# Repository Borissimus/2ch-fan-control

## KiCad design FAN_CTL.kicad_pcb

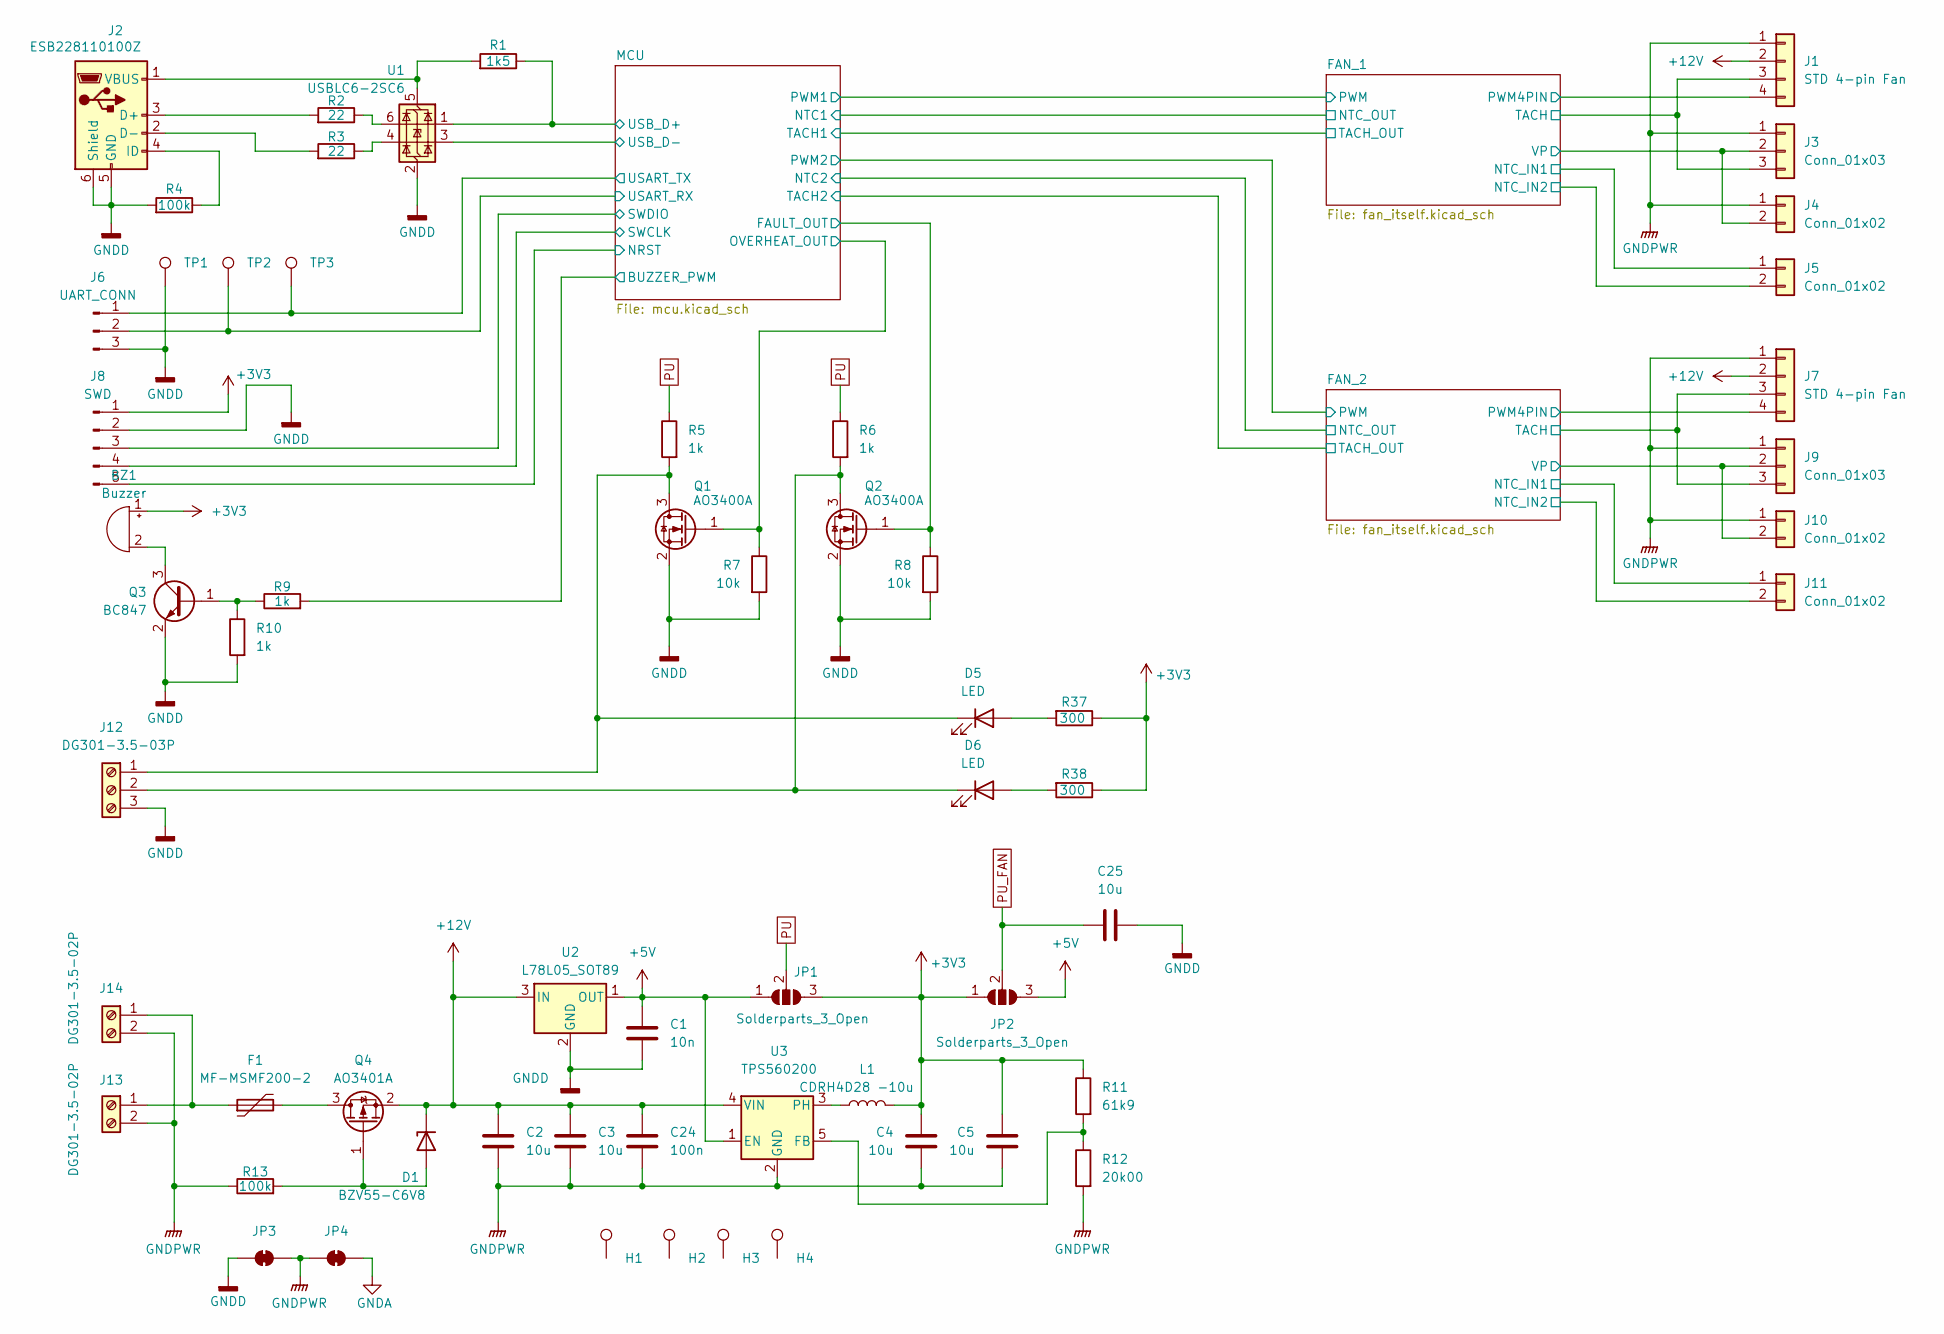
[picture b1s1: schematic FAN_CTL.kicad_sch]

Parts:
BZ1: Buzzer; Buzzer_TDK_PS1240P02BT_D12.2mm_H6.5mm
C1: 10n; C_0805_2012Metric
C2, C3, C4, C5, C25: 10u; C_0805_2012Metric
C24: 100n; C_0805_2012Metric
D1: BZV55-C6V8; D_MiniMELF
D5, D6: LED; LED_0805_2012Metric
F1: MF-MSMF200-2; Fuse_1812_4532Metric
H1, H2, H3, H4: parts; parts_3.2mm_M3_Pad_Via
J1, J7: STD 4-pin Fan; FanPinHeader_1x04_P2.54mm_Vertical
J2: ESB228110100Z; USB_Micro-B_Molex_47346-0001
J3, J9: Conn_01x03; FanPinHeader_1x03_P2.54mm_Vertical
J4, J10: Conn_01x02; JST_XH_B2B-XH-A_1x02_P2.50mm_Vertical
J5, J11: Conn_01x02; JST_PH_B2B-PH-K_1x02_P2.00mm_Vertical
J6: UART_CONN; PinHeader_1x03_P2.54mm_Vertical
J8: SWD; PinHeader_1x05_P2.54mm_Vertical
J12: DG301-3.5-03P; DG350-3_5-03P
J13, J14: DG301-3.5-02P; DG350-3_5-02P
JP1, JP2: Solderparts_3_Open; Solderparts-3_P1.3mm_Open_RoundedPad1.0x1.5mm
JP3, JP4: Solderparts_2_Bridged; Solderparts-2_P1.3mm_Bridged_Pad1.0x1.5mm
L1: CDRH4D28 -10u; CDRH4D28
Q1, Q2: AO3400A; SOT-23
Q3: BC847; SOT-23
Q4: AO3401A; SOT-23
R1: 1k5; R_0805_2012Metric
R2, R3: 22; R_0805_2012Metric
R4, R13: 100k; R_0805_2012Metric
R5, R6, R9, R10: 1k; R_0805_2012Metric
R7, R8: 10k; R_0805_2012Metric
R11: 61k9; R_0805_2012Metric
R12: 20k00; R_0805_2012Metric
R37, R38: 300; R_0805_2012Metric
TP1, TP2, TP3: parts; parts_Pad_D1.0mm
U1: USBLC6-2SC6; SOT-23-6
U2: L78L05_SOT89; SOT-89-3
U3: TPS560200; SOT-23-5

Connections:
+3.3VA: J5.1, J11.1; also elsewhere on the board
+3V3: BZ1.1 (+), C4.1, C5.1, J8.1, JP1.3 (B), JP2.1 (A), L1.2, R11.1, R37.1, R38.1; also elsewhere on the board
+5V: C1.1, JP1.1 (A), JP2.3 (B), U2.1 (OUT), U3.1 (EN)
+12V: C2.1, C3.1, C24.1, D1.1 (K), J1.2, J7.2, Q4.2 (S), U2.3 (IN), U3.4 (VIN); also elsewhere on the board
/FAN_1/NTC_IN2: J5.2; also elsewhere on the board
/FAN_1/PWM4PIN: J1.4; also elsewhere on the board
/FAN_1/TACH: J1.3, J3.3; also elsewhere on the board
/FAN_1/VP: J3.2, J4.2; also elsewhere on the board
/FAN_2/NTC_IN2: J11.2; also elsewhere on the board
/FAN_2/PWM4PIN: J7.4; also elsewhere on the board
/FAN_2/TACH: J7.3, J9.3; also elsewhere on the board
/FAN_2/VP: J9.2, J10.2; also elsewhere on the board
/MCU/BUZZER_PWM: R9.2; also elsewhere on the board
/MCU/FAULT_OUT: Q2.1 (G), R8.1; also elsewhere on the board
/MCU/NRST: J8.5; also elsewhere on the board
/MCU/OVERHEAT_OUT: Q1.1 (G), R7.1; also elsewhere on the board
/MCU/SWCLK: J8.4; also elsewhere on the board
/MCU/SWDIO: J8.3; also elsewhere on the board
/MCU/USART_RX: J6.2, TP2.1 (1_1); also elsewhere on the board
/MCU/USART_TX: J6.1, TP3.1 (1_1); also elsewhere on the board
/MCU/USB_D+: R1.1, U1.1 (I/O1); also elsewhere on the board
/MCU/USB_D-: U1.3 (I/O2); also elsewhere on the board
GNDA: JP4.2 (B); also elsewhere on the board
GNDD: C1.2, C25.2, J2.5 (GND), J2.6 (Shield), J6.3, J8.2, J12.3, JP3.1 (A), Q1.2 (S), Q2.2 (S), Q3.2 (E), R4.2, R7.2, R8.2, R10.2, TP1.1 (1_1), U1.2 (GND), U2.2 (GND); also elsewhere on the board
GNDPWR: C2.2, C3.2, C4.2, C5.2, C24.2, J1.1, J3.1, J4.1, J7.1, J9.1, J10.1, J13.2, J14.2, JP3.2 (B), JP4.1 (A), R12.2, R13.1, U3.2 (GND); also elsewhere on the board
unnamed: BZ1.2 (-), Q3.3 (C)
unnamed: D1.2 (A), Q4.1 (G), R13.2
unnamed: D5.2 (A), R37.2
unnamed: D5.1 (K), J12.1, Q1.3 (D), R5.2
unnamed: D6.2 (A), R38.2
unnamed: D6.1 (K), J12.2, Q2.3 (D), R6.2
unnamed: J2.3 (D+), R2.2
unnamed: J2.2 (D-), R3.2
unnamed: J2.4 (ID), R4.1
unnamed: J2.1 (VBUS), R1.2, U1.5 (VBUS)
unnamed: F1.1, J13.1, J14.1
unnamed: Q3.1 (B), R9.1, R10.1
unnamed: F1.2, Q4.3 (D)
unnamed: R2.1, U1.6 (I/O1)
unnamed: R3.1, U1.4 (I/O2)
unnamed: R11.2, R12.1, U3.5 (FB)
unnamed: L1.1, U3.3 (PH)
PU: JP1.2 (C), R5.1, R6.1
PU_FAN: C25.1, JP2.2 (C); also elsewhere on the board

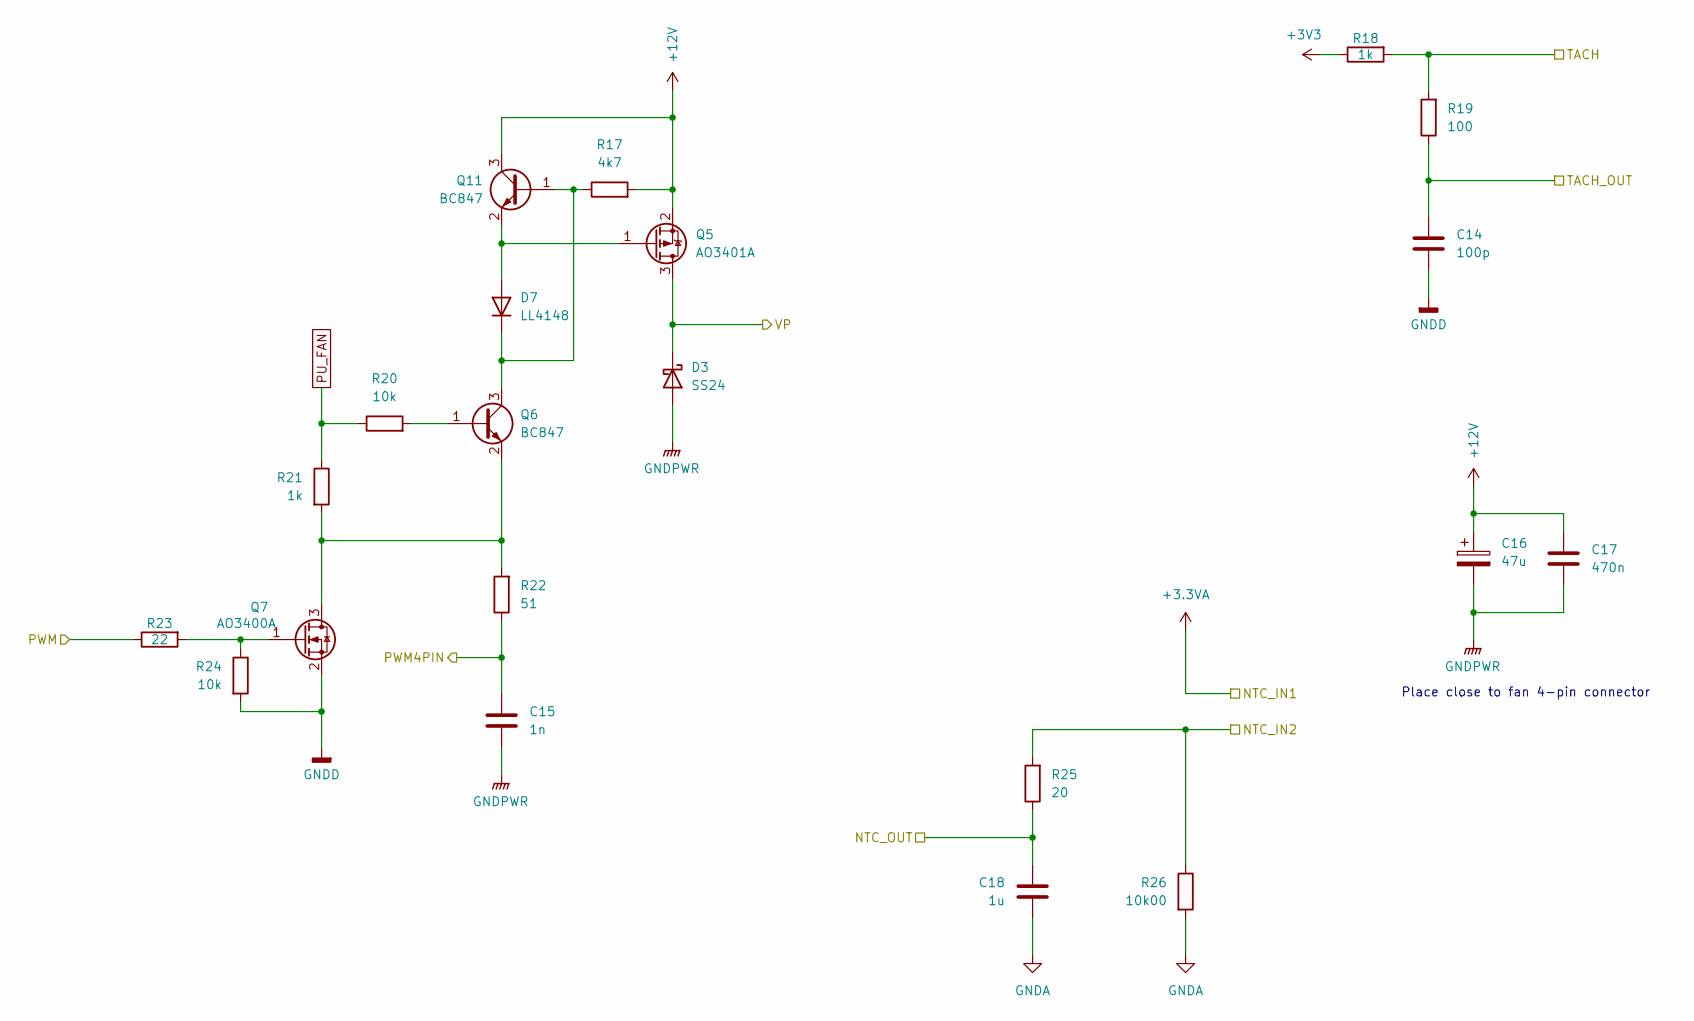
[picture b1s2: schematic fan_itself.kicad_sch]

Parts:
C14: 100p; C_0805_2012Metric
C15: 1n; C_0805_2012Metric
C16: 47u; CP_Radial_D5.0mm_P2.50mm
C17: 470n; C_0805_2012Metric
C18: 1u; C_0402_1005Metric
D3: SS24; D_SMA
D7: LL4148; D_MiniMELF
Q5: AO3401A; SOT-23
Q6, Q11: BC847; SOT-23
Q7: AO3400A; SOT-23
R17: 4k7; R_0805_2012Metric
R18, R21: 1k; R_0805_2012Metric
R19: 100; R_0805_2012Metric
R20, R24: 10k; R_0805_2012Metric
R22: 51; R_0805_2012Metric
R23: 22; R_0805_2012Metric
R25: 20; R_0402_1005Metric
R26: 10k00; R_0402_1005Metric

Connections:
+3V3: R18.1; also elsewhere on the board
+12V: C16.1, C17.1, Q5.2 (S), Q11.3 (C), R17.2; also elsewhere on the board
/FAN_1/NTC_IN2: R25.2, R26.1; also elsewhere on the board
/FAN_1/NTC_OUT: C18.1, R25.1; also elsewhere on the board
/FAN_1/PWM: R23.1; also elsewhere on the board
/FAN_1/PWM4PIN: C15.1, R22.1; also elsewhere on the board
/FAN_1/TACH: R18.2, R19.2; also elsewhere on the board
/FAN_1/TACH_OUT: C14.1, R19.1; also elsewhere on the board
/FAN_1/VP: D3.1 (K), Q5.3 (D); also elsewhere on the board
GNDA: C18.2, R26.2; also elsewhere on the board
GNDD: C14.2, Q7.2 (S), R24.2; also elsewhere on the board
GNDPWR: C15.2, C16.2, C17.2, D3.2 (A); also elsewhere on the board
unnamed: D7.2 (A), Q5.1 (G), Q11.2 (E)
unnamed: D7.1 (K), Q6.3 (C), Q11.1 (B), R17.1
unnamed: Q6.1 (B), R20.2
unnamed: Q6.2 (E), Q7.3 (D), R21.2, R22.2
unnamed: Q7.1 (G), R23.2, R24.1
PU_FAN: R20.1, R21.1; also elsewhere on the board

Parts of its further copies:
C19: 100p; C_0805_2012Metric
C20: 1n; C_0805_2012Metric
C21: 47u; CP_Radial_D5.0mm_P2.50mm
C22: 470n; C_0805_2012Metric
C23: 1u; C_0402_1005Metric
D4: SS24; D_SMA
D8: LL4148; D_MiniMELF
Q8: AO3401A; SOT-23
Q9, Q12: BC847; SOT-23
Q10: AO3400A; SOT-23
R27: 4k7; R_0805_2012Metric
R28, R31: 1k; R_0805_2012Metric
R29: 100; R_0805_2012Metric
R30, R34: 10k; R_0805_2012Metric
R32: 51; R_0805_2012Metric
R33: 22; R_0805_2012Metric
R35: 20; R_0402_1005Metric
R36: 10k00; R_0402_1005Metric

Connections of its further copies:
+3V3: R28.1; also elsewhere on the board
+12V: C21.1, C22.1, Q8.2 (S), Q12.3 (C), R27.2; also elsewhere on the board
/FAN_2/NTC_IN2: R35.2, R36.1; also elsewhere on the board
/FAN_2/NTC_OUT: C23.1, R35.1; also elsewhere on the board
/FAN_2/PWM: R33.1; also elsewhere on the board
/FAN_2/PWM4PIN: C20.1, R32.1; also elsewhere on the board
/FAN_2/TACH: R28.2, R29.2; also elsewhere on the board
/FAN_2/TACH_OUT: C19.1, R29.1; also elsewhere on the board
/FAN_2/VP: D4.1 (K), Q8.3 (D); also elsewhere on the board
GNDA: C23.2, R36.2; also elsewhere on the board
GNDD: C19.2, Q10.2 (S), R34.2; also elsewhere on the board
GNDPWR: C20.2, C21.2, C22.2, D4.2 (A); also elsewhere on the board
unnamed: D8.2 (A), Q8.1 (G), Q12.2 (E)
unnamed: D8.1 (K), Q9.3 (C), Q12.1 (B), R27.1
unnamed: Q9.1 (B), R30.2
unnamed: Q9.2 (E), Q10.3 (D), R31.2, R32.2
unnamed: Q10.1 (G), R33.2, R34.1
PU_FAN: R30.1, R31.1; also elsewhere on the board

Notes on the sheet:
Place close to fan 4-pin connector

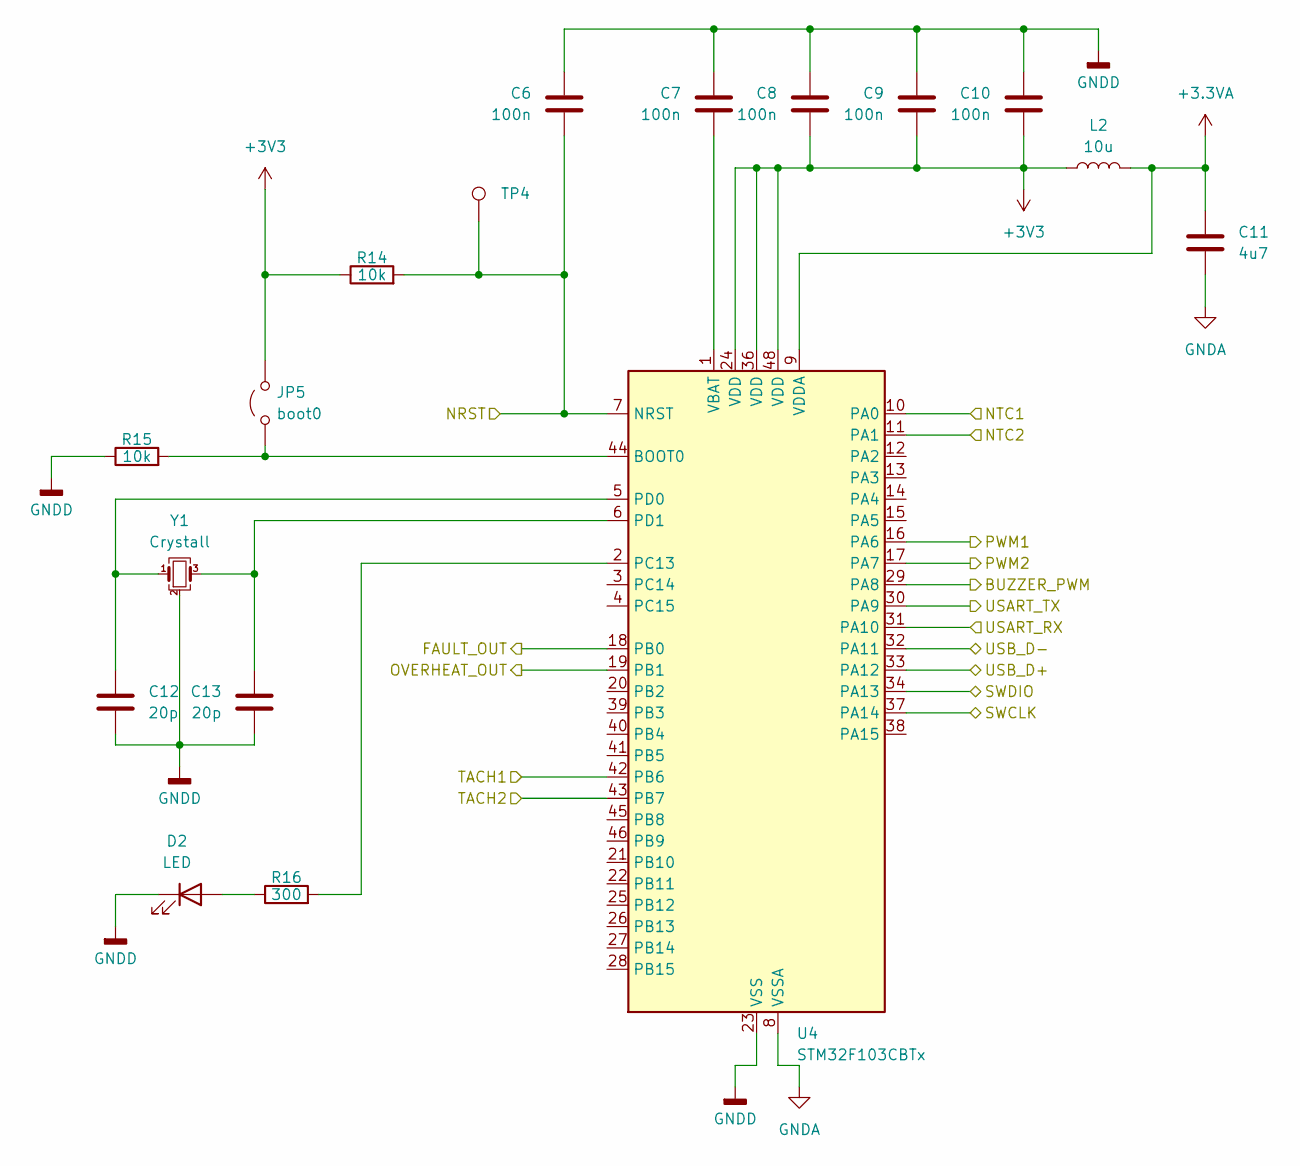
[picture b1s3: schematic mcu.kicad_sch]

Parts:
C6, C7, C8, C9, C10: 100n; C_0402_1005Metric
C11: 4u7; C_0603_1608Metric
C12, C13: 20p; C_0402_1005Metric
D2: LED; LED_0805_2012Metric
JP5: boot0; PinHeader_1x02_P2.54mm_Vertical
L2: 10u; L_1210_3225Metric
R14, R15: 10k; R_0805_2012Metric
R16: 300; R_0805_2012Metric
TP4: parts; parts_Pad_D1.0mm
U4: STM32F103CBTx; LQFP-48_7x7mm_P0.5mm
Y1: Crystall; Crystal_SMD_5032-4Pin_5.0x3.2mm

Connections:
+3.3VA: C11.1, L2.2, U4.9 (VDDA); also elsewhere on the board
+3V3: C8.2, C9.2, C10.2, JP5.2 (B), L2.1, R14.1, U4.24 (VDD), U4.36 (VDD), U4.48 (VDD); also elsewhere on the board
/FAN_1/NTC_OUT: U4.10 (PA0); also elsewhere on the board
/FAN_1/PWM: U4.16 (PA6); also elsewhere on the board
/FAN_1/TACH_OUT: U4.42 (PB6); also elsewhere on the board
/FAN_2/NTC_OUT: U4.11 (PA1); also elsewhere on the board
/FAN_2/PWM: U4.17 (PA7); also elsewhere on the board
/FAN_2/TACH_OUT: U4.43 (PB7); also elsewhere on the board
/MCU/BUZZER_PWM: U4.29 (PA8); also elsewhere on the board
/MCU/FAULT_OUT: U4.18 (PB0); also elsewhere on the board
/MCU/NRST: C6.2, R14.2, TP4.1 (1_1), U4.7 (NRST); also elsewhere on the board
/MCU/OVERHEAT_OUT: U4.19 (PB1); also elsewhere on the board
/MCU/SWCLK: U4.37 (PA14); also elsewhere on the board
/MCU/SWDIO: U4.34 (PA13); also elsewhere on the board
/MCU/USART_RX: U4.31 (PA10); also elsewhere on the board
/MCU/USART_TX: U4.30 (PA9); also elsewhere on the board
/MCU/USB_D+: U4.33 (PA12); also elsewhere on the board
/MCU/USB_D-: U4.32 (PA11); also elsewhere on the board
GNDA: C11.2, U4.8 (VSSA); also elsewhere on the board
GNDD: C6.1, C7.1, C8.1, C9.1, C10.1, C12.1, C13.1, D2.1 (K), R15.1, U4.23 (VSS), U4.35 (VSS), U4.47 (VSS), Y1.2 (G), Y1.4 (G); also elsewhere on the board
unnamed: D2.2 (A), R16.1
unnamed: JP5.1 (A), R15.2, U4.44 (BOOT0)
unnamed: R16.2, U4.2 (PC13)
unnamed: C12.2, U4.5 (PD0), Y1.1
unnamed: C13.2, U4.6 (PD1), Y1.3
unnamed: C7.2, U4.1 (VBAT)

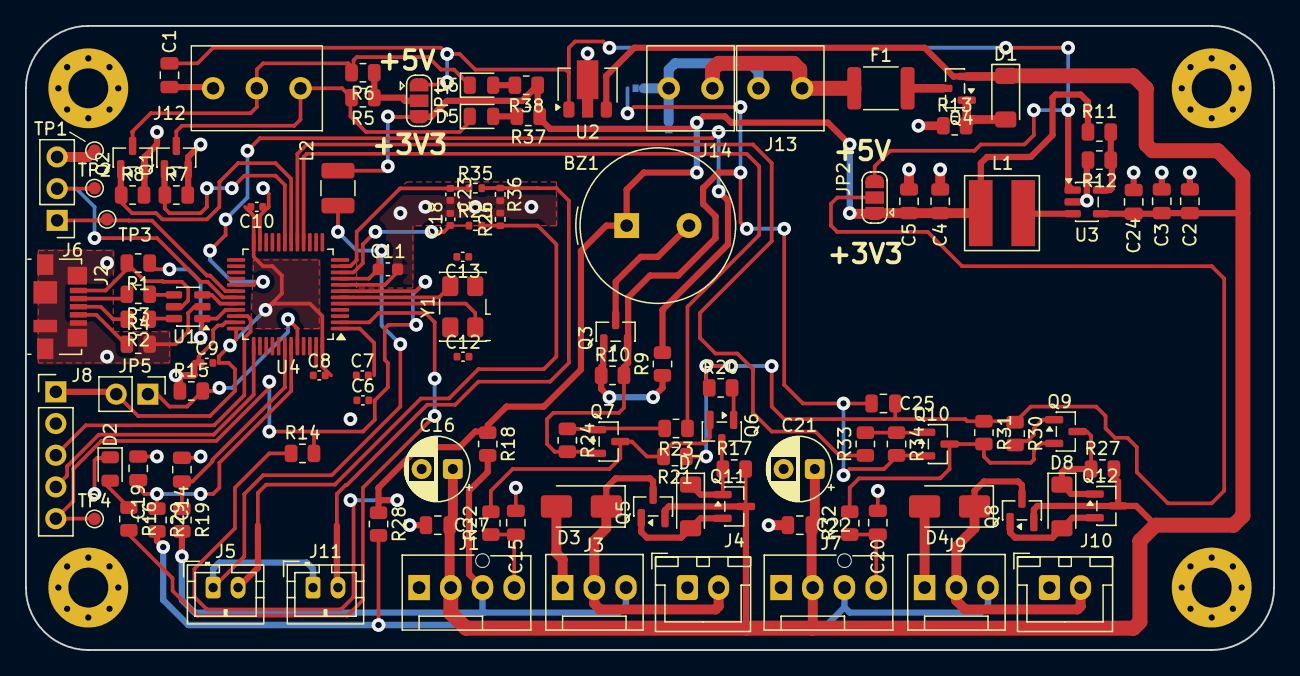
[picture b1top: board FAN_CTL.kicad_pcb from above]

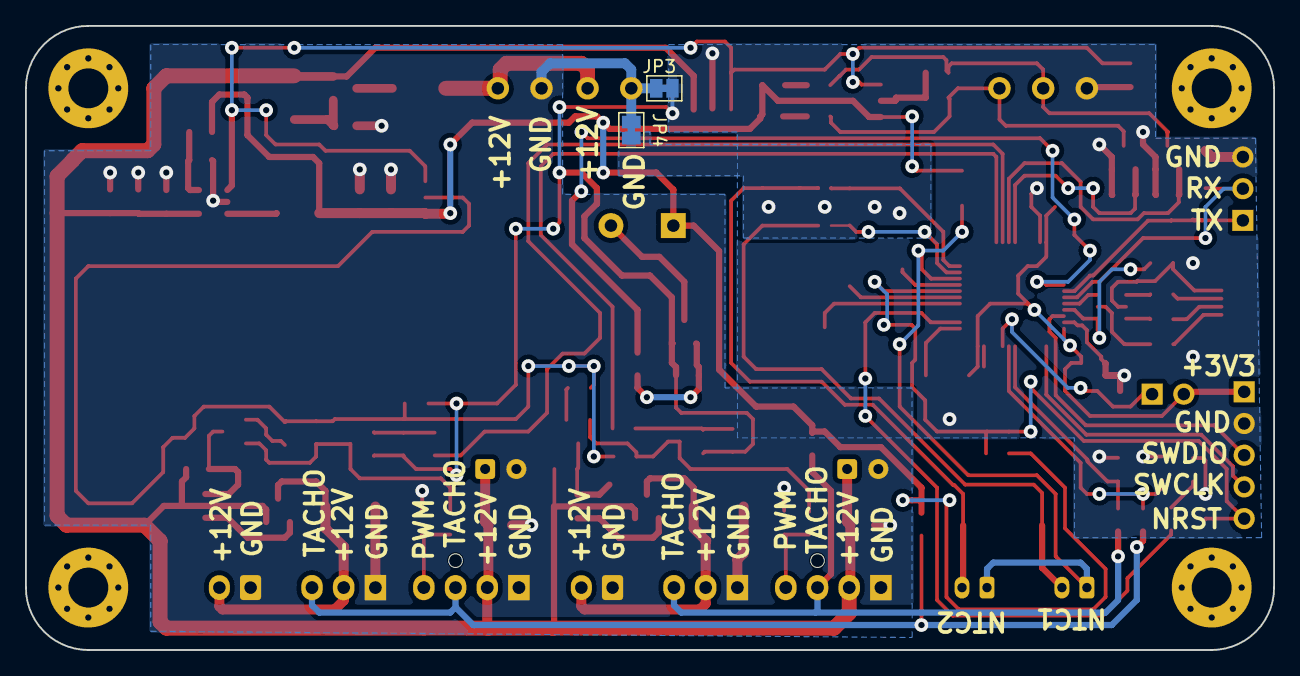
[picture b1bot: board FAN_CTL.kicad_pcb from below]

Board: 2 copper layers, 100.0 x 50.0 mm, 119 parts (2 on the bottom side), 66 nets.
